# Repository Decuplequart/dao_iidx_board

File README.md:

# DAO Controller Board

DAO系IIDXコントローラーの既存ボタン、ターンテーブルセンサー、LEDハーネスを再利用し、USB HIDおよびBluetooth Low Energy HIDへの対応を目指す交換用コントローラー基板です。

本リポジトリには、KiCadで作成した回路図・PCBデータ、プロジェクト固有ライブラリ、およびJLCPCB向け製造データ生成に必要な設定を収録します。

Repository: https://github.com/Decuplequart/dao_iidx_board

> [!WARNING]
> この基板は現在 **Rev.1の試作段階** です。実機での完全な動作確認、長時間運転、全LED同時点灯時の温度評価、USB/BLEファームウェア検証は完了していません。製造・実装・使用は自己責任で行ってください。

## 主な機能

- 7鍵入力
- START / SELECT入力
- 2相ターンテーブルセンサー入力（RD1 / RD2）
- USB 2.0 Full-Speed HID対応を想定
- Bluetooth Low Energy HID対応を想定
- DAO系単色ボタンLED 9系統の個別制御
- RESETボタン
- MODE / PAIRボタン
- SWD書き込み端子
- 8 GPIOの拡張端子
- USB Type-C給電
- モバイルバッテリー給電によるBLE運用を想定

## 設計方針

この基板は内蔵バッテリーを搭載せず、USB Type-Cからの5V給電に統一しています。

- 有線使用時: PCとのUSB通信および給電
- 無線使用時: BLE通信および外部モバイルバッテリーからの給電

内蔵LiPo、充電回路、昇圧回路を省略することで、回路の簡略化、安全性の向上、保守性の改善を狙っています。

## ハードウェア構成

### マイコン

- Raytac `MDBT50Q-1MV2`
- Nordic Semiconductor `nRF52840`搭載
- USB / BLE対応
- チップアンテナ内蔵
- SWD経由で初回書き込み可能

JLCPCB/LCSC部品番号:

```text
C5118826
```

この部品は通常在庫ではなく、事前注文が必要になる場合があります。また、ブートローダーやアプリケーションが未書き込みの可能性があるため、SWD書き込みを前提としてください。

### LEDドライバ

- Texas Instruments `TLC6C598PWR` × 2
- 8ch DMOSオープンドレイン出力
- 2個をカスケード接続し、9系統を使用

DAO系単色ボタンLEDの実測電流は1灯あたり約40～50mAでした。LED電源は5V、ドライバ出力はローサイドシンク方式です。

```text
U2 DRAIN0～7 -> LED_K1～LED_K8
U3 DRAIN0    -> LED_K9
```

### 電源

```text
USB Type-C VBUS
  -> VBUS_5V
     -> MDBT50Q VDDH / VBUS
     -> TLC6C598 × 2
     -> KEY_LED_5V
     -> SCR_5V
     -> DISH_LED_5V
```

- 内蔵バッテリーなし
- USB Type-C受電用CC抵抗: 5.1kΩ × 2
- キーLED共通電源は太配線で分配
- 裏面GNDゾーンを使用

## GPIO割り当て

| 機能 | nRF52840 GPIO |
|---|---|
| K1 | P0.02 |
| K2 | P0.03 |
| K3 | P0.04 |
| K4 | P0.05 |
| K5 | P0.28 |
| K6 | P0.29 |
| K7 | P0.30 |
| START | P0.00 |
| SELECT | P0.01 |
| MODE_PAIR | P0.06 |
| RD1 | P0.13 |
| RD2 | P0.14 |
| LED_DATA | P0.15 |
| LED_CLK | P0.16 |
| LED_LATCH | P0.17 |
| RESET | P0.18 / nRESET |

### 拡張GPIO

`GPIO_EXPANSION`端子へ次の8本を引き出しています。

```text
EXP0 -> P0.19
EXP1 -> P0.20
EXP2 -> P0.21
EXP3 -> P0.22
EXP4 -> P0.23
EXP5 -> P0.24
EXP6 -> P0.25
EXP7 -> P0.26
```

将来のPS2対応や追加I/Oへの利用を想定していますが、現時点では用途・ファームウェアとも未確定です。

## コネクター

| 機能 | 種類 |
|---|---|
| DISH_LED | JST XH 2極、2.50mm、垂直 |
| KEY1～KEY7 | JST XH 4極、2.50mm、垂直 |
| START / SELECT | JST XH 4極、2.50mm、垂直 |
| DISH_SENSOR | JST XH 4極、2.50mm、垂直 |
| SWD | 1×4、2.54mmピンヘッダー |
| GPIO_EXPANSION | 2×5、2.54mmピンヘッダー |

キー・START・SELECT用4極コネクターの基本構成:

```text
Pin 1: スイッチ入力
Pin 2: LED制御端子（LOWで点灯）
Pin 3: KEY_LED_5V
Pin 4: GND
```

実際の既存ハーネスを接続する前に、必ず導通とピン順を確認してください。

## SWD端子

```text
J3 Pin 1: +3V3 / VTref
J3 Pin 2: SWDIO
J3 Pin 3: SWDCLK
J3 Pin 4: GND
```

J-Link、nRF52840 DK、またはJLCPCBのプログラミングサービスを使った初回書き込みを想定しています。

## 基板仕様

```text
基板外形: 80.00 mm × 57.00 mm
層数: 2層
推奨板厚: 1.6 mm
銅厚: 1 oz
固定穴: 4個、5.5 mm NPTH
```

固定穴中心位置は、基板左上を `(0, 0)` とした場合、次のとおりです。

```text
左上: ( 4.5, 15.0 ) mm
右上: (75.5, 15.0 ) mm
左下: ( 4.5, 45.0 ) mm
右下: (75.5, 45.0 ) mm
```

## アンテナ領域の注意

`MDBT50Q-1MV2`のアンテナKEEP OUT内には、表裏とも次を配置しないでください。

- 銅箔ゾーン
- 配線
- ビア
- 部品
- 金属スペーサー
- ネジや金属板

Gerber出力後、アンテナ領域からGNDベタが正しく抜けていることを必ず確認してください。

## 主なJLCPCB/LCSC部品

| リファレンス | 部品 | LCSC番号 |
|---|---|---|
| C1, C3, C4, C6 | 100nF / 16V / 0402 | C1525 |
| C2, C5 | 4.7uF / 16V / 0603 | C19666 |
| D1 | 1SS404 / SOD-323 | C2847422 |
| D2 | SS14 / SMA | C2480 |
| R1 | 0Ω / 0402 | C17168 |
| R2, R3 | 5.1kΩ / 0402 | C25905 |
| R4, R5 | 10kΩ / 0402 | C25744 |
| R6, R7 | 1kΩ / 0402 | C11702 |
| SW1, SW2 | SMDタクトスイッチ | C49234124 |
| U1 | MDBT50Q-1MV2 | C5118826 |
| U2, U3 | TLC6C598PWR | C2863406 |
| USB-C | TYPE-C-31-M-12 | C165948 |
| J1 | JST B2B-XH-A | C158012 |
| J3 | 1×4 2.54mmピンヘッダー | C5116483 |
| J4 | 2×5 2.54mmピンヘッダー | C492422 |
| J5～J14 | JST B4B-XH-A | C144395 |

> [!NOTE]
> 在庫、価格、Basic/Extended区分、Standard PCBA対応状況は変動します。発注直前にJLCPCBの部品ページと実装プレビューで再確認してください。

## リポジトリ構成

```text
.
├─ *.kicad_pro              KiCadプロジェクト
├─ *.kicad_sch              回路図
├─ *.kicad_pcb              PCB
├─ *.kicad_sym              プロジェクト固有シンボル
├─ *.pretty/                プロジェクト固有フットプリント
├─ *.3dshapes/              3Dモデル
├─ fp-lib-table             フットプリントライブラリ設定
├─ sym-lib-table            シンボルライブラリ設定
└─ README.md
```

3Dモデルは製造そのものには必須ではありません。Gerber、ドリル、BOM、CPLの内容を優先してください。

## 製造データの生成

KiCad用`JLCPCB Tools`プラグインを使用する場合:

1. PCBエディターでDRCを実行
2. エラー0、未配線0を確認
3. GNDゾーンを再計算
4. JLCPCB Toolsを開く
5. 各実装部品へLCSC番号を割り当て
6. 固定穴とテストポイントをBOM/POSから除外
7. `Generate`を実行

PCBA発注に必要な主なファイル:

```text
Gerber + Drill ZIP
BOM.csv
CPL / Positions.csv
```

発注時はJLCPCBのプレビューで、少なくとも次を確認してください。

- U1、U2、U3の1番ピン方向
- D1、D2のカソード方向
- USB Type-Cの向き
- JST-XHコネクターの向き
- タクトスイッチの位置
- SMT部品の回転角
- PTH/NPTH穴
- アンテナKEEP OUT
- 表裏シルク

## ファームウェア

ファームウェアは別途開発予定です。

想定機能:

- USB HIDゲームコントローラー
- BLE HIDゲームコントローラー
- 7鍵、START、SELECT入力
- ターンテーブル2相入力
- LED制御
- MODE / PAIR操作
- 将来の拡張GPIO利用

初回書き込みはSWDを使用します。JLCPCBへ書き込みを依頼する場合は、対象デバイス、SWD端子定義、書き込み対象HEX、Erase/Program/Verify手順を明記してください。

## 既知の注意事項

- Rev.1は未検証です。
- DAO系コントローラーの世代やモデルにより、ハーネスのピン配列が異なる可能性があります。
- LED電流は実機で約40～50mA/灯を観測しています。
- 9灯同時点灯時はLEDだけで約360～450mAになる可能性があります。
- モバイルバッテリーによっては低負荷時に自動停止する場合があります。
- U1は事前注文、Standard PCBA、X線検査が必要になる場合があります。
- U1が未書き込み品の場合、SWD経由の初回書き込みが必要です。
- 未確認の状態でPC、コントローラー、既存ハーネスへ接続しないでください。

## ライセンス

本リポジトリの内容は、特に明記がない限り **MIT License** の下で公開します。

詳細は[`LICENSE`](LICENSE)を参照してください。

## Disclaimer

本プロジェクトは非公式の個人製作物です。DAO、JLCPCB、LCSC、Raytac、Nordic Semiconductor、Texas Instruments、JSTその他の各社とは関係ありません。各名称および商標は、それぞれの権利者に帰属します。

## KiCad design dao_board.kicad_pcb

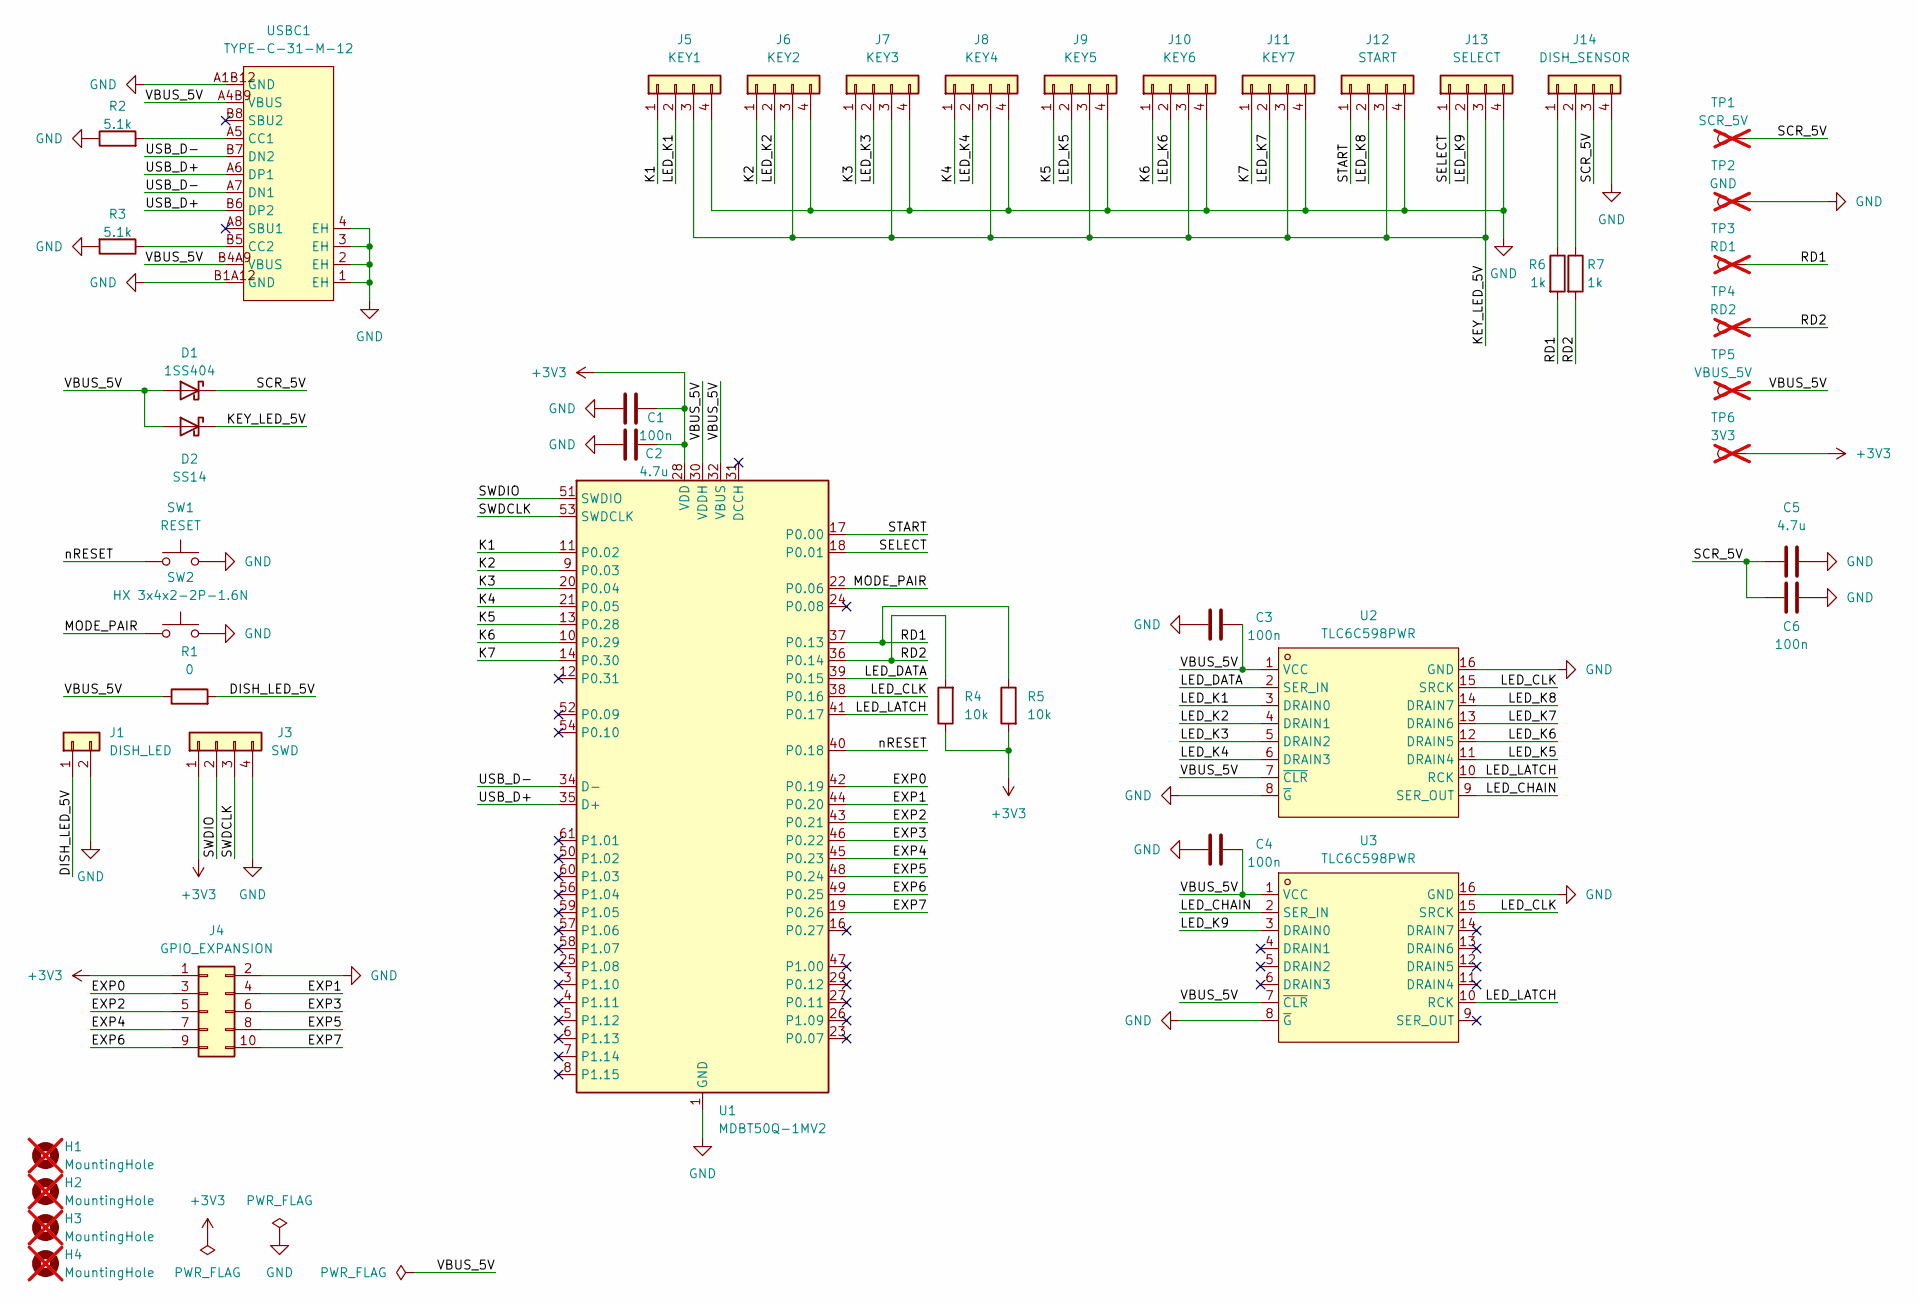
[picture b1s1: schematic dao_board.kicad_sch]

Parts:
C1, C3, C4, C6: 100n; C_0402_1005Metric; LCSC C1525
C2, C5: 4.7u; C_0603_1608Metric; LCSC C19666
D1: 1SS404; D_SOD-323; LCSC C2847422
D2: SS14; D_SMA; LCSC C2480
H1, H2, H3, H4: MountingHole; MountingHole_M5; not fitted
J1: DISH_LED; JST_XH_B2B-XH-A_1x02_P2.50mm_Vertical; LCSC C158012
J3: SWD; FanPinHeader_1x04_P2.54mm_Vertical; LCSC C5116483
J4: GPIO_EXPANSION; PinHeader_2x05_P2.54mm_Vertical; LCSC C492422
J5: KEY1; JST_XH_B4B-XH-A_1x04_P2.50mm_Vertical; LCSC C144395
J6: KEY2; JST_XH_B4B-XH-A_1x04_P2.50mm_Vertical; LCSC C144395
J7: KEY3; JST_XH_B4B-XH-A_1x04_P2.50mm_Vertical; LCSC C144395
J8: KEY4; JST_XH_B4B-XH-A_1x04_P2.50mm_Vertical; LCSC C144395
J9: KEY5; JST_XH_B4B-XH-A_1x04_P2.50mm_Vertical; LCSC C144395
J10: KEY6; JST_XH_B4B-XH-A_1x04_P2.50mm_Vertical; LCSC C144395
J11: KEY7; JST_XH_B4B-XH-A_1x04_P2.50mm_Vertical; LCSC C144395
J12: START; JST_XH_B4B-XH-A_1x04_P2.50mm_Vertical; LCSC C144395
J13: SELECT; JST_XH_B4B-XH-A_1x04_P2.50mm_Vertical; LCSC C144395
J14: DISH_SENSOR; JST_XH_B4B-XH-A_1x04_P2.50mm_Vertical; LCSC C144395
R1: 0; R_0402_1005Metric; LCSC C17168
R2, R3: 5.1k; R_0402_1005Metric; LCSC C25905
R4, R5: 10k; R_0402_1005Metric; LCSC C25744
R6, R7: 1k; R_0402_1005Metric; LCSC C11702
SW1: RESET; KEY-SMD_L4.0-W3.0-LS4.9-1; LCSC C49234124
SW2: HX 3x4x2-2P-1.6N; KEY-SMD_L4.0-W3.0-LS4.9-1; LCSC C49234124
TP1: SCR_5V; TestPoint_Pad_D2.0mm; not fitted
TP2: GND; TestPoint_Pad_D2.0mm; not fitted
TP3: RD1; TestPoint_Pad_D2.0mm; not fitted
TP4: RD2; TestPoint_Pad_D2.0mm; not fitted
TP5: VBUS_5V; TestPoint_Pad_D2.0mm; not fitted
TP6: 3V3; TestPoint_Pad_D2.0mm; not fitted
U1: MDBT50Q-1MV2; Raytac_MDBT50Q_FIXED; LCSC Part C5118826
U2, U3: TLC6C598PWR; TSSOP-16_L5.0-W4.4-P0.65-LS6.4-BL; MPN TLC6C598PWR; LCSC Part C2863406
USBC1: TYPE-C-31-M-12; USB-C_SMD-TYPE-C-31-M-12_1_FIXED; MPN TYPE-C-31-M-12; LCSC Part C165948

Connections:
+3V3: C1.2, C2.2, J3.1, J4.1, R4.1, R5.2, TP6.1 (1_1), U1.28 (VDD)
/DISH_LED_5V: J1.1, R1.2
/EXP0: J4.3, U1.42 (P0.19)
/EXP1: J4.4, U1.44 (P0.20)
/EXP2: J4.5, U1.43 (P0.21)
/EXP3: J4.6, U1.46 (P0.22)
/EXP4: J4.7, U1.45 (P0.23)
/EXP5: J4.8, U1.48 (P0.24)
/EXP6: J4.9, U1.49 (P0.25)
/EXP7: J4.10, U1.19 (P0.26)
/K1: J5.1, U1.11 (P0.02)
/K2: J6.1, U1.9 (P0.03)
/K3: J7.1, U1.20 (P0.04)
/K4: J8.1, U1.21 (P0.05)
/K5: J9.1, U1.13 (P0.28)
/K6: J10.1, U1.10 (P0.29)
/K7: J11.1, U1.14 (P0.30)
/KEY_LED_5V: D2.1 (K), J5.3, J6.3, J7.3, J8.3, J9.3, J10.3, J11.3, J12.3, J13.3
/LED_CHAIN: U2.9 (SER_OUT), U3.2 (SER_IN)
/LED_CLK: U1.38 (P0.16), U2.15 (SRCK), U3.15 (SRCK)
/LED_DATA: U1.39 (P0.15), U2.2 (SER_IN)
/LED_K1: J5.2, U2.3 (DRAIN0)
/LED_K2: J6.2, U2.4 (DRAIN1)
/LED_K3: J7.2, U2.5 (DRAIN2)
/LED_K4: J8.2, U2.6 (DRAIN3)
/LED_K5: J9.2, U2.11 (DRAIN4)
/LED_K6: J10.2, U2.12 (DRAIN5)
/LED_K7: J11.2, U2.13 (DRAIN6)
/LED_K8: J12.2, U2.14 (DRAIN7)
/LED_K9: J13.2, U3.3 (DRAIN0)
/LED_LATCH: U1.41 (P0.17), U2.10 (RCK), U3.10 (RCK)
/MODE_PAIR: SW2.1, U1.22 (P0.06)
/RD1: R5.1, R6.2, TP3.1 (1_1), U1.37 (P0.13)
/RD2: R4.2, R7.2, TP4.1 (1_1), U1.36 (P0.14)
/SCR_5V: C5.1, C6.1, D1.1 (K), J14.3, TP1.1 (1_1)
/SELECT: J13.1, U1.18 (P0.01)
/START: J12.1, U1.17 (P0.00)
/SWDCLK: J3.3, U1.53 (SWDCLK)
/SWDIO: J3.2, U1.51 (SWDIO)
/USB_D+: U1.35 (D+), USBC1.A6 (DP1), USBC1.B6 (DP2)
/USB_D-: U1.34 (D-), USBC1.A7 (DN1), USBC1.B7 (DN2)
/VBUS_5V: C3.2, C4.2, D1.2 (A), D2.2 (A), R1.1, TP5.1 (1_1), U1.30 (VDDH), U1.32 (VBUS), U2.1 (VCC), U2.7 (~CLR), U3.1 (VCC), U3.7 (~CLR), USBC1.A4B9 (VBUS), USBC1.B4A9 (VBUS)
/nRESET: SW1.1, U1.40 (P0.18)
GND: C1.1, C2.1, C3.1, C4.1, C5.2, C6.2, J1.2, J3.4, J4.2, J5.4, J6.4, J7.4, J8.4, J9.4, J10.4, J11.4, J12.4, J13.4, J14.4, R2.1, R3.2, SW1.2, SW2.2, TP2.1 (1_1), U1.1 (GND), U1.2 (GND), U1.15 (GND), U1.33 (GND), U1.55 (GND), U2.8 (~G), U2.16 (GND), U3.8 (~G), U3.16 (GND), USBC1.1 (EH), USBC1.2 (EH), USBC1.3 (EH), USBC1.4 (EH), USBC1.A1B12 (GND), USBC1.B1A12 (GND)
unnamed: J14.1, R6.1
unnamed: J14.2, R7.1
unnamed: R2.2, USBC1.A5 (CC1)
unnamed: R3.1, USBC1.B5 (CC2)

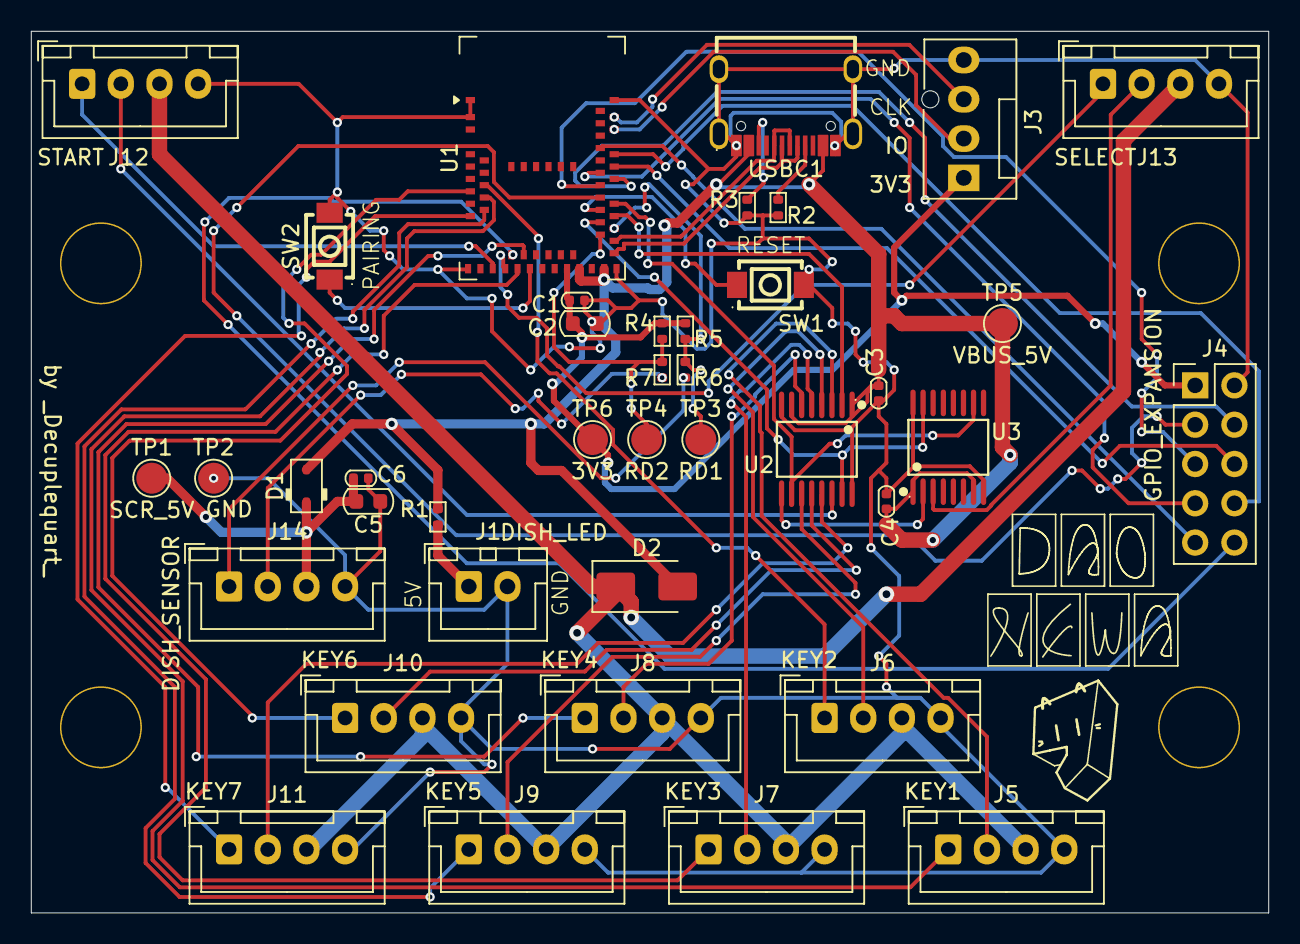
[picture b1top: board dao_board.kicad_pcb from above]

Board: 2 copper layers, 80.0 x 57.0 mm, 44 parts (0 on the bottom side), 48 nets.

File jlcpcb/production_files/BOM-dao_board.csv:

Comment,Designator,Footprint,LCSC,Quantity
0,R1,R_0402_1005Metric,C17168,1
100n,"C1,C3,C4,C6",C_0402_1005Metric,C1525,4
10k,"R4,R5",R_0402_1005Metric,C25744,2
1SS404,D1,D_SOD-323,C2847422,1
1k,"R6,R7",R_0402_1005Metric,C11702,2
4.7u,"C2,C5",C_0603_1608Metric,C19666,2
5.1k,"R2,R3",R_0402_1005Metric,C25905,2
DISH_LED,J1,JST_XH_B2B-XH-A_1x02_P2.50mm_Vertical,C158012,1
DISH_SENSOR,J14,JST_XH_B4B-XH-A_1x04_P2.50mm_Vertical,C144395,1
GPIO_EXPANSION,J4,PinHeader_2x05_P2.54mm_Vertical,C492422,1
HX 3x4x2-2P-1.6N,SW2,KEY-SMD_L4.0-W3.0-LS4.9-1,C49234124,1
KEY1,J5,JST_XH_B4B-XH-A_1x04_P2.50mm_Vertical,C144395,1
KEY2,J6,JST_XH_B4B-XH-A_1x04_P2.50mm_Vertical,C144395,1
KEY3,J7,JST_XH_B4B-XH-A_1x04_P2.50mm_Vertical,C144395,1
KEY4,J8,JST_XH_B4B-XH-A_1x04_P2.50mm_Vertical,C144395,1
KEY5,J9,JST_XH_B4B-XH-A_1x04_P2.50mm_Vertical,C144395,1
KEY6,J10,JST_XH_B4B-XH-A_1x04_P2.50mm_Vertical,C144395,1
KEY7,J11,JST_XH_B4B-XH-A_1x04_P2.50mm_Vertical,C144395,1
MDBT50Q-1MV2,U1,Raytac_MDBT50Q_FIXED,C5118826,1
RESET,SW1,KEY-SMD_L4.0-W3.0-LS4.9-1,C49234124,1
SELECT,J13,JST_XH_B4B-XH-A_1x04_P2.50mm_Vertical,C144395,1
SS14,D2,D_SMA,C2480,1
START,J12,JST_XH_B4B-XH-A_1x04_P2.50mm_Vertical,C144395,1
SWD,J3,FanPinHeader_1x04_P2.54mm_Vertical,C5116483,1
TLC6C598PWR,"U2,U3",TSSOP-16_L5.0-W4.4-P0.65-LS6.4-BL,C2863406,2
TYPE-C-31-M-12,USBC1,USB-C_SMD-TYPE-C-31-M-12_1_FIXED,C165948,1
